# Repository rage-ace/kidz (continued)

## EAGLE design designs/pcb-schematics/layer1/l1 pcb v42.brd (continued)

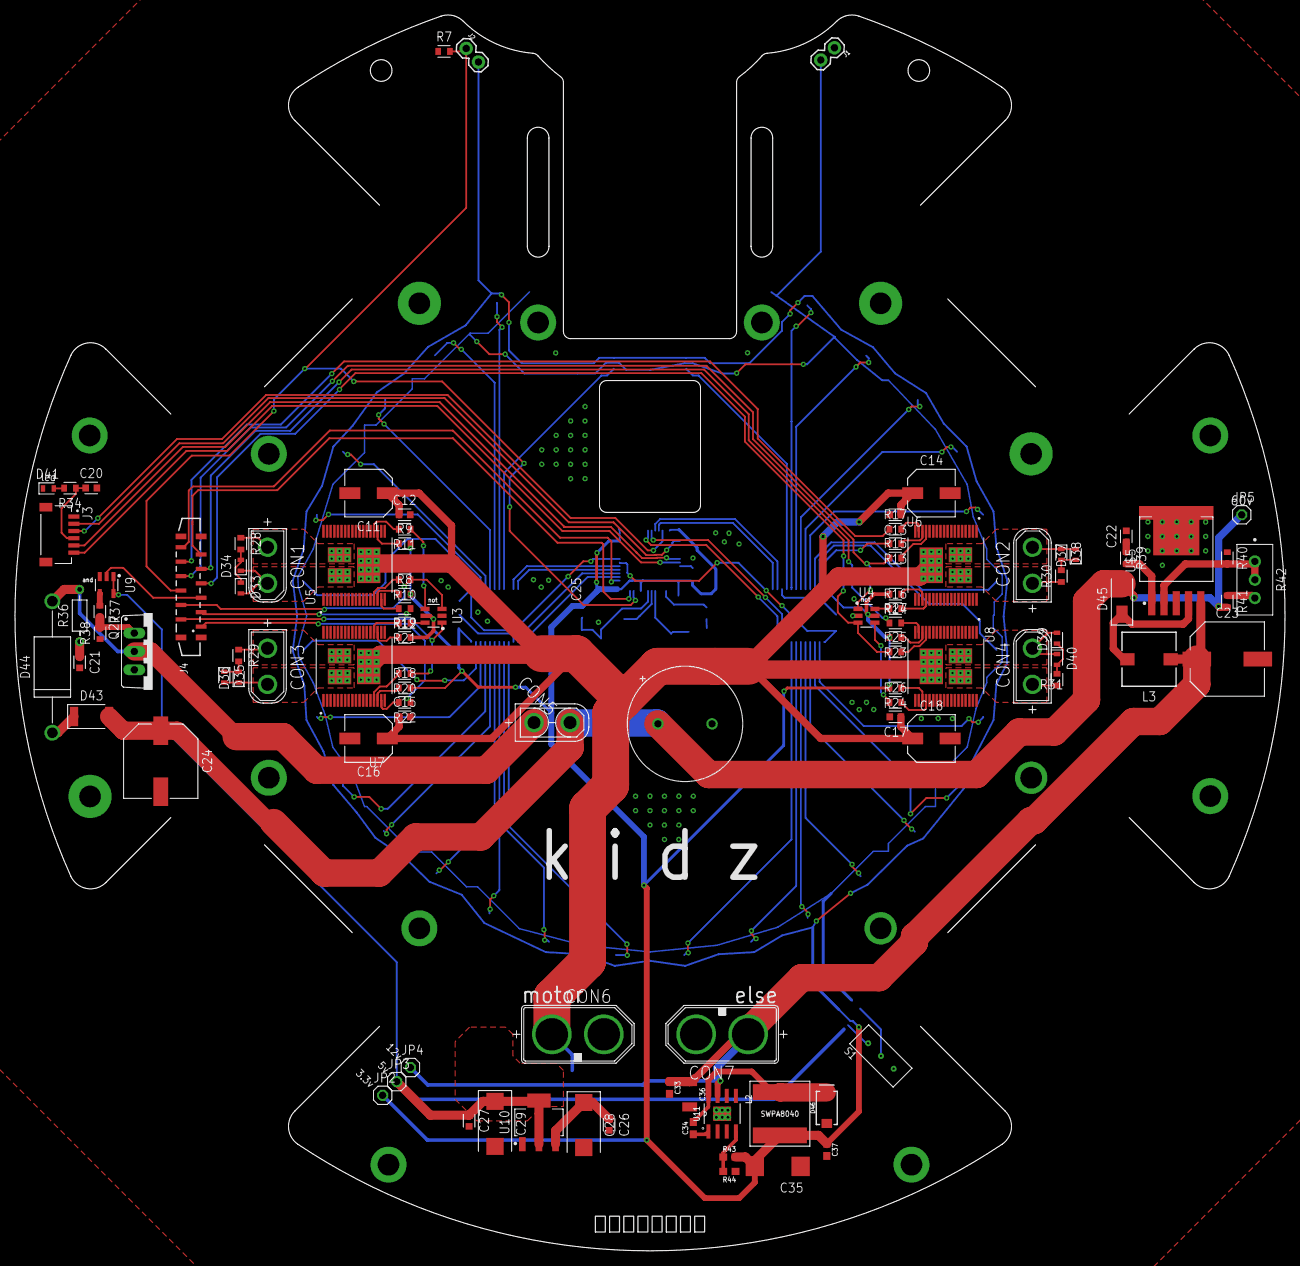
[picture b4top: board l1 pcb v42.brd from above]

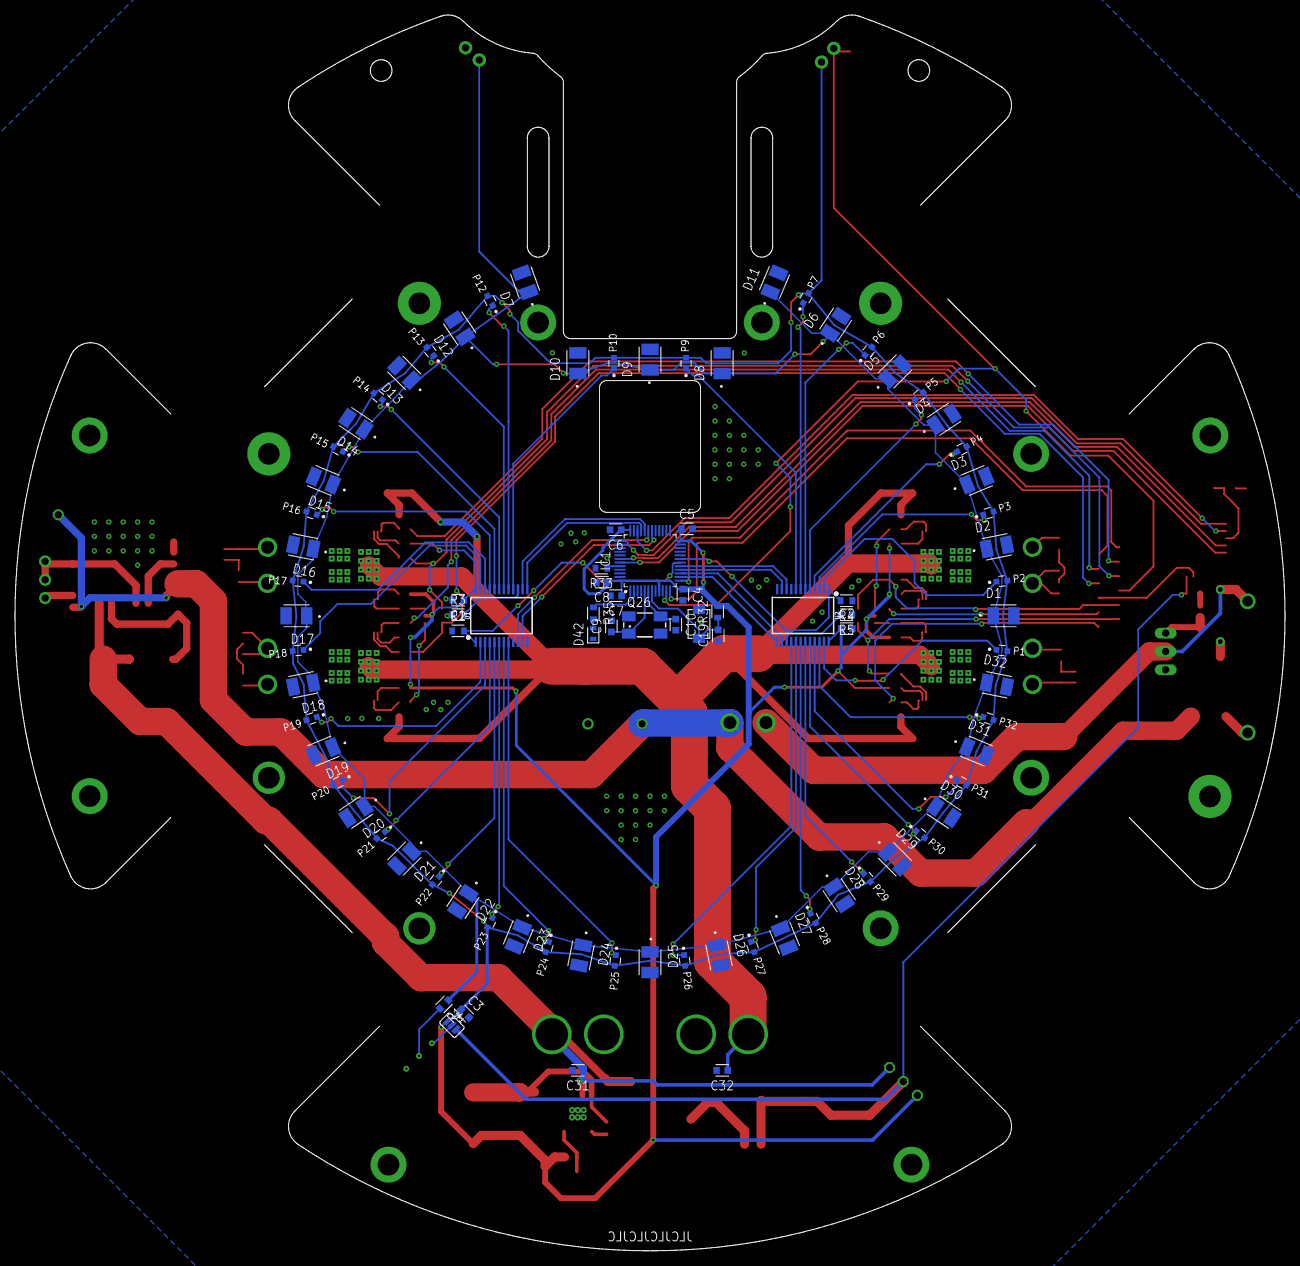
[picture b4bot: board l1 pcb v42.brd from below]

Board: 2 copper layers, 176.0 x 171.3 mm, 190 parts (90 on the bottom side), 125 nets.

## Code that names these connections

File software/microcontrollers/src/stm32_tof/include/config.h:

#ifndef STM32_TOF_CONFIG_H
#define STM32_TOF_CONFIG_H

#include <VL53L1X.h>
#include <array>
#include <cstdint>
#include <stm32f103c_variant_generic.h>

// #define DEBUG

// Baud Rates
#define BLUETOOTH_BAUD_RATE 9600
#define DEBUG_BAUD_RATE     115200

// Pins
#define PIN_LED_DEBUG PC13
#define PIN_RX_DEBUG  PB7
#define PIN_TX_DEBUG  PB6

#define PIN_RX PA3
#define PIN_TX PA2

#define PIN_RX_BLUETOOTH PB11
#define PIN_TX_BLUETOOTH PB10

#define PIN_SDA_TOF PB9
#define PIN_SCL_TOF PB8

#define PIN_XSHUT_FRONT PB14
#define PIN_XSHUT_BACK  PB2
#define PIN_XSHUT_LEFT  PA11
#define PIN_XSHUT_RIGHT PB12

#define PIN_RING      PA9
#define PIN_LEFT_EYE  PB0
#define PIN_RIGHT_EYE PB1

// Tell the compiler the specific pins each HardwareSerial uses
#ifdef DEBUG
    #define PIN_DEBUG_SERIAL_RX PB7
    #define PIN_DEBUG_SERIAL_TX PB6
    #define DEBUG_SERIAL        Serial1
#endif

#define PIN_TEENSY_SERIAL_RX PA3
#define PIN_TEENSY_SERIAL_TX PA2
#define TEENSY_SERIAL        Serial2

#define PIN_BLUETOOTH_SERIAL_RX PB11
#define PIN_BLUETOOTH_SERIAL_TX PB10
#define BLUETOOTH_SERIAL        Serial3

// EEPROM Addresses

// I2C Addresses
#define I2C_ADDRESS_TOF_START 0x2A

// Time-Of-Flight Sensors
// Read: https://www.pololu.com/product/3415
struct TOFConfig {
    uint8_t xshutPin;
    VL53L1X::DistanceMode distanceMode; // Short, Medium, Long
    uint16_t measurementPeriod;         // in us, 20 ms to 50 ms for Short,
                                        // 33 ms to 50 ms for Medium and Long
    uint8_t intermeasurementPeriod;     // in ms, at least measurementPeriod
};

#define TOF_COUNT 4
const std::array<TOFConfig, TOF_COUNT> TOF_CONFIGS = {{
    {PIN_XSHUT_FRONT, VL53L1X::Short, 20000, 20}, // Front
    {PIN_XSHUT_BACK, VL53L1X::Short, 20000, 20},  // Back
    {PIN_XSHUT_LEFT, VL53L1X::Short, 20000, 20},  // Left
    {PIN_XSHUT_RIGHT, VL53L1X::Short, 20000, 20}  // Right
}};

#endif

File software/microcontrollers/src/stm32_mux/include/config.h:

#ifndef STM32_MUX_CONFIG_H
#define STM32_MUX_CONFIG_H

#include <array>
#include <cstdint>
#include <stm32f103c_variant_generic.h>

#include "shared_config.h"

// #define DEBUG

// Baud Rates
#define DEBUG_BAUD_RATE 115200

// Pins
#define PIN_LED_DEBUG PA8
#define PIN_RX_DEBUG  PB7
#define PIN_TX_DEBUG  PB6

#define PIN_RX PA3
#define PIN_TX PA2

#define PIN_LIGHTGATE PA1

#define PIN_LDRMUX1_SIG PB0
#define PIN_LDRMUX1_S0  PA10
#define PIN_LDRMUX1_S1  PA9
#define PIN_LDRMUX1_S2  PA11
#define PIN_LDRMUX1_S3  PA12

#define PIN_LDRMUX2_SIG PB1
#define PIN_LDRMUX2_S0  PA7
#define PIN_LDRMUX2_S1  PA6
#define PIN_LDRMUX2_S2  PA5
#define PIN_LDRMUX2_S3  PA4

// Tell the compiler the specific pins each HardwareSerial uses
#ifdef DEBUG
    #define PIN_DEBUG_SERIAL_RX PB7
    #define PIN_DEBUG_SERIAL_TX PB6
    #define DEBUG_SERIAL        Serial1
#endif

#define PIN_TEENSY_SERIAL_RX PA3
#define PIN_TEENSY_SERIAL_TX PA2
#define TEENSY_SERIAL        Serial2

// Light Sensor Config
enum LDRMUX { MUX1 = 0x00, MUX2 = 0x01 };

#define LDR_CALIBRATION_DURATION   10000 // In milliseconds
#define LDR_CALIBRATION_MULTIPLIER 0.7

#define LDR_PIN_COUNT 16 * 2 // The number of possible input pins on the MUXs
#define LDR_COUNT     30     // The number of actual photodiodes below the robot
const std::array<uint8_t, LDR_PIN_COUNT> LDR_MAP = {
    255, 14, 13, 12, 11, 10, 9,  8,  7,  6,  5,  4,  3,  2,  1,  0,
    255, 29, 28, 27, 26, 25, 24, 23, 22, 21, 20, 19, 18, 17, 16, 15,
};
const std::array<uint8_t, LDR_COUNT> LDR_MAP_REVERSE = {
    15, 14, 13, 12, 11, 10, 9,  8,  7,  6,  5,  4,  3,  2,  1,
    31, 30, 29, 28, 27, 26, 25, 24, 23, 22, 21, 20, 19, 18, 17,
};
const std::array<float, LDR_COUNT> LDR_BEARINGS = {
    8.1461,   26.9079,  39.7366,  51.1272,  61.88670, 73.1367,
    84.3867,  95.6367,  106.8867, 118.1367, 129.1957, 141.0268,
    152.4409, 162.7907, 174.2699, 185.7539, 197.2331, 208.3438,
    219.6814, 231.0705, 241.8867, 253.1367, 264.3867, 275.6367,
    286.8867, 298.1367, 309.2879, 320.4649, 333.8737, 351.8859,
};
// // Computer Lab (multiplier=0.7), L1 A
// const std::array<uint16_t, LDR_COUNT> LDR_THRESHOLDS = {
//     3536, 3481, 3511, 3517, 3519, 3531, 3536, 3526, 3609, 3643,
//     3591, 3545, 3592, 1872, 3534, 3602, 3455, 3550, 3593, 3555,
//     3394, 3313, 3195, 3347, 3285, 3217, 3200, 3200, 3183, 3238,
// };
// // Home, L1 A
// const std::array<uint16_t, LDR_COUNT> LDR_THRESHOLDS = {
//     3160, 3125, 3147, 3144, 3150, 3116, 3172, 3152, 3364, 3361,
//     3146, 3173, 3295, 1507, 3206, 3232, 3020, 3162, 3280, 3143,
//     2882, 2901, 2747, 2609, 2874, 2763, 2797, 2687, 2735, 2660,
// };
// Home, L1 B
const std::array<uint16_t, LDR_COUNT> LDR_THRESHOLDS = {
    3182, 3145, 3242, 3081, 3210, 2971, 2927, 3082, 3116, 3294,
    3305, 3209, 3322, 3411, 3062, 3957, 3368, 3946, 3329, 3338,
    3330, 3335, 3318, 3294, 3453, 3226, 3378, 1757, 2971, 2958,
};
#define LDR_ACTIVATION_THRESHOLD 3

#endif

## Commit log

2023-03-01 Add existing code
2023-03-01 Add coral directory
2023-03-01 Create folder for PCB schematics
2023-03-01 Update PCB directory structure
2023-03-01 Implement holonomic movement
2023-03-01 Refactor
2023-03-01 Remove redundant LineData.isPresent
2023-03-17 Refactor code, fix bug in movement, and code IMU
2023-03-18 Refactor code and add TOF code
2023-03-18 Add bluetooth code and clean up STM32 serial
2023-03-18 Calculate loop times
2023-03-18 Add keep straight code
2023-03-18 Refactor teensy code and drive motors when calibrating IMU
2023-03-18 Refactor code to use angle instead of bearing
2023-03-18 Abstract and refactor utility functions
2023-03-29 Did a lot of stuff
2023-03-30 Got robot angle controller working reliably
2023-04-01 Move Teensy code into Sensors and Movement classes
2023-04-01 Use PacketSerial with COBS and add line control
2023-04-04 Add camera code
2023-04-04 Update CameraData payload on Teensy side
2023-04-04 Update READMEs
2023-04-07 Add dribbler and kicker code
2023-04-07 Implement localisation algorithm and fine tune other parts
2023-04-07 Fix minor coral bugs
2023-04-07 Made "side of boundary" sensing very robust
2023-04-07 Print goal location in debug output
2023-04-07 Migrate coral code onto new clean flash
2023-04-08 Tune ball kalman filter (a little)
2023-04-08 Update camera parameters
2023-04-08 Implement kalman filter for goals
2023-04-08 Fix some bugs and got localisation working
2023-04-09 Log uncaught exceptions
2023-04-09 Fix a few bugs here and there, basically finish calibrating ball curve and robot heading, and implement wall avoidance
2023-04-09 Fix disable autofocus and update parameters
2023-04-11 Add multiplier to light sensor threshold calibration
2023-04-11 Fix kicker
2023-04-11 Refactor teensy code organisation
2023-04-11 Update dribbler values and improve localisation
2023-04-12 Improve calibration
2023-04-13 Calibrate camera for bot 2
2023-04-13 Update bot 1 camera calibration
2023-04-13 Make massive changes to goalie and striker code
2023-04-14 Add science centre calibrations
2024-01-07 added l1 elec files
2024-01-07 added l2 elec files
2024-01-07 added l3 elec files
2024-01-07 added l4 elec files
2024-01-07 Rename l1 pcb v38.pdf to l1.pdf
2024-01-07 Rename l1 pcb v42.brd to l1.brd
2024-01-07 Rename l1_pcb_v38.sch to l1.sch
2024-01-07 RENAME
2024-01-07 CHANGEED pdfs because fusion export pdf encoding was WRONG
